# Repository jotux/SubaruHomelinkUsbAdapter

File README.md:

## Subaru Homelink mirror USB power adapter

This is a simple device to step-down the 12V used by the Homelink mirror in my Subaru to 5V and output it to a USB cable. This can technically work for any mirror that has 12V and GND.

I measured the regulator efficiency around 88% for the camera load (250-500mA).

## Schematic

## Board

## Installed

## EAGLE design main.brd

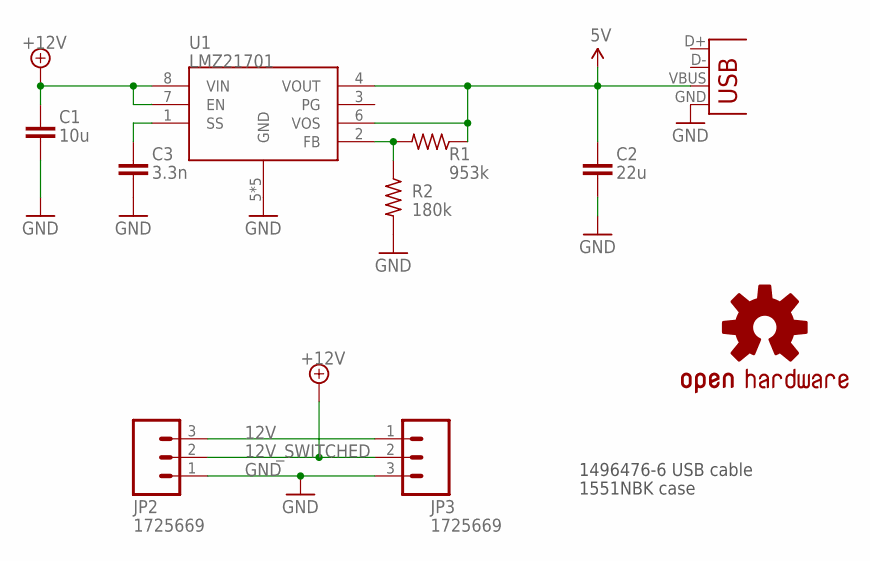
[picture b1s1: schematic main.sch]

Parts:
C1: 10u; C1206
C2: 22u; C1206
C3: 3.3n; C0603
JP1: 62900416021; USB-A-S-SILK-FEMALE
JP2, JP3: 1725669; 1X03
LOGO1: OSHW-LOGOL; OSHW-LOGO-L
R1: 953k; R0603
R2: 180k; R0603
U1: LMZ21701

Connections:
5V: C2.1, JP1.VBUS, R1.1, U1.4 (VOUT), U1.6 (VOS)
12V: JP2.3, JP3.1
12V_SWITCHED: C1.1, JP2.2, JP3.2, U1.7 (EN), U1.8 (VIN)
GND: C1.2, C2.2, C3.2, JP1.GND, JP2.1, JP3.3, R2.2, U1.5 (GND), U1.G1 (GND), U1.G1V (GND), U1.G2 (GND), U1.G2V (GND)
unnamed: C3.1, U1.1 (SS)
unnamed: R1.2, R2.1, U1.2 (FB)

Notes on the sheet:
1496476-6 USB cable
1551NBK case

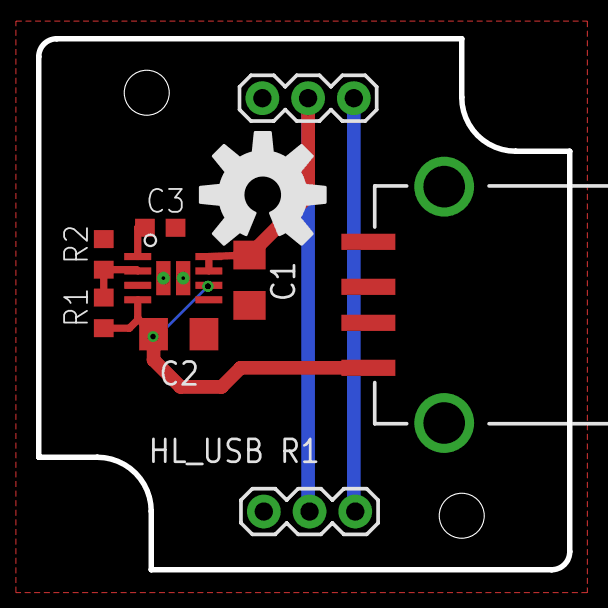
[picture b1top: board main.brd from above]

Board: 2 copper layers, 29.5 x 29.5 mm, 11 parts (1 on the bottom side), 6 nets.

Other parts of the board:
U$2: LOGO

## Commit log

2015-02-09 initial
2015-02-11 Finished layout
2015-02-12 Rev 0 complete, BOM and gerber added
2015-04-01 Switch linear regulator for switching.
2015-06-16 Update readme, add pics
2015-06-16 Resize some picss
2015-06-16 Move stuff around
2015-06-16 Add note about wrong net name.
2015-06-16 Note about eff.
2015-06-16 Remove note, since the second ground wire is 12V, enabled only when in reverse

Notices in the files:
parts and their libraries:
SparkFun-Connectors: Licensing: Creative Commons ShareAlike 4.0 International - https://creativecommons.org/licenses/by-sa/4.0
